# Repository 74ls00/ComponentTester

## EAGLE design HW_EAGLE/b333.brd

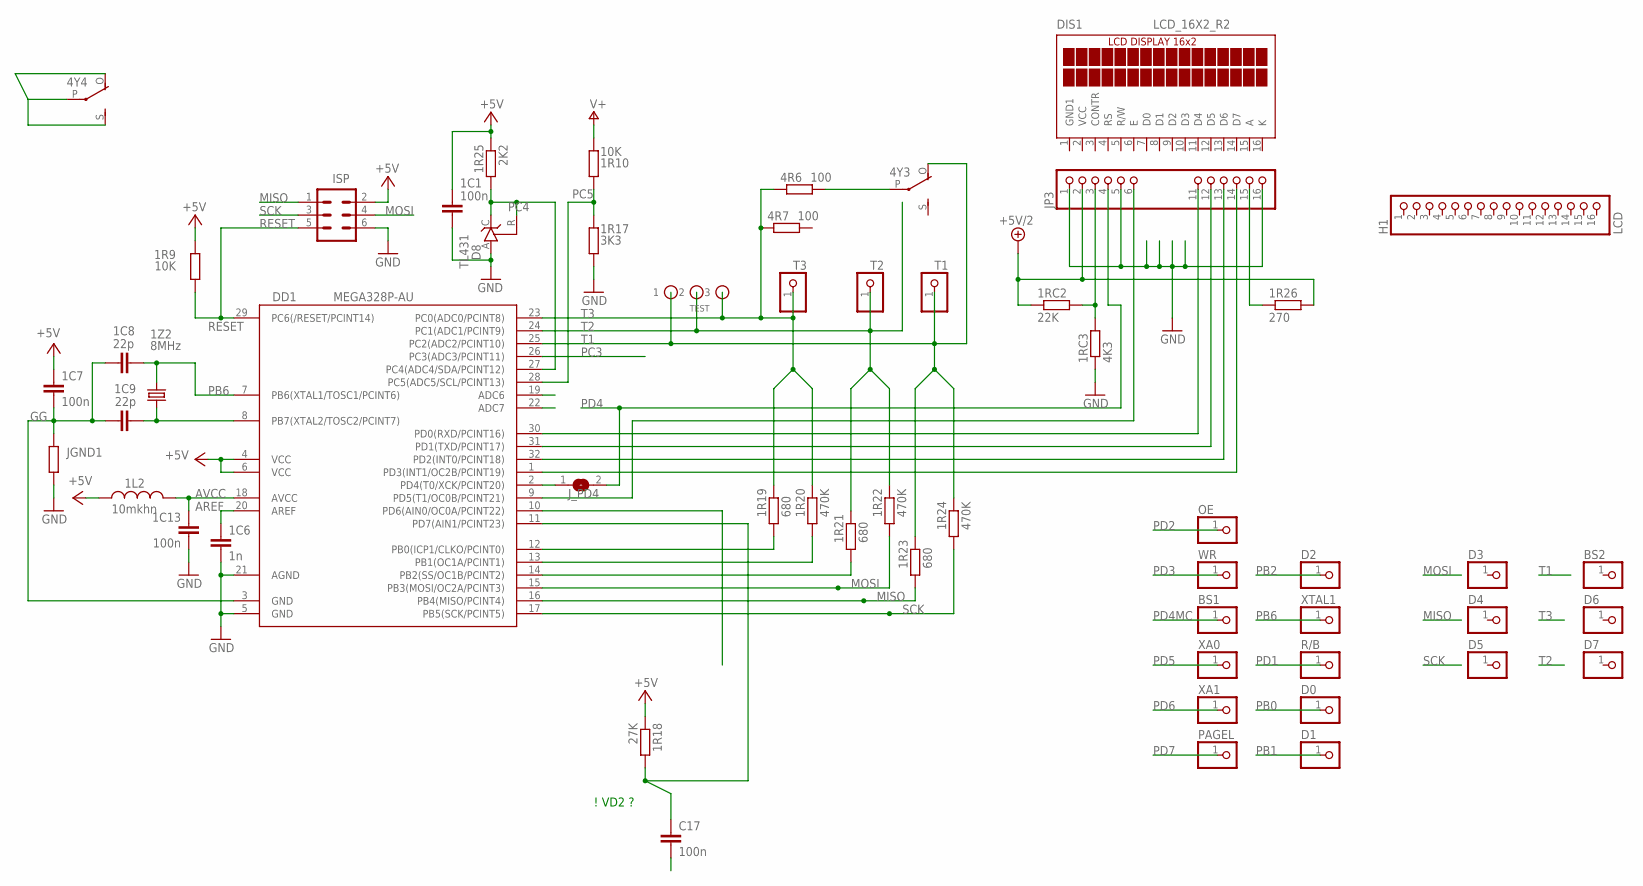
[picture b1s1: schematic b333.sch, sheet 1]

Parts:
1C1, 1C7, 1C13: 100n; C0805K
1C6: 1n; C0805K
1C8, 1C9: 22p; C0805K
1L2: 10mkhn; IRF36
1R9, 1R10: 10K; R0805
1R17: 3K3; R1206W
1R18: 27K; R0805
1R19, 1R21, 1R23: 680; M0805
1R20, 1R22, 1R24: 470K; M0805
1R25: 2K2; R0805
1R26: 270; R0805
1RC2: 22K; R0805
1RC3: 4K3; R1206W
1Z2: 8MHz; HC49U70
4R6, 4R7: 100; R0805
4Y3, 4Y4: РЭС55А
BS1, BS2: PINHD-1X1; 1X01
C17: 100n; C0805K
D0, D1, D2, D3, D4, D5, D6, D7: PINHD-1X1; 1X01
D8: TL431; TO92-CLP
DD1: MEGA328P-AU; TQFP32-08
DIS1: LCD_16X2_R2
H1: LCD; 1X16
ISP: MA03-2
JGND1: R-EU_R1206W; R1206W
JP3: PINHD-X16-8; 1X16-8
J_PD4: SJ
OE: PINHD-1X1; 1X01
PAGEL: PINHD-1X1; 1X01
R/B: PINHD-1X1; 1X01
T1, T2, T3: PINHD-1X1; 1X01
TEST: TT-P
WR: PINHD-1X1; 1X01
XA0, XA1: PINHD-1X1; 1X01
XTAL1: PINHD-1X1; 1X01

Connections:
+5V: 1C1.1, 1C7.1, 1L2.2, 1R9.2, 1R18.1, 1R25.1, DD1.4 (VCC), DD1.6 (VCC), ISP.2; also elsewhere on the board
+5V/2: 1R26.2, 1RC2.1, JP3.2; also elsewhere on the board
ADC6: DD1.19 (ADC6)
ADC7: DD1.22 (ADC7)
AREF: 1C6.1, DD1.20 (AREF)
AVCC: 1C13.1, 1L2.1, DD1.18 (AVCC)
GG: 1C7.2, 1C8.1, 1C9.1, DD1.3 (GND), JGND1.2
GND: 1C1.2, 1C6.2, 1C13.2, 1R17.1, 1RC3.1, C17.2, D8.A, DD1.5 (GND), DD1.21 (AGND), ISP.6, JGND1.1, JP3.1, JP3.5, JP3.16; also elsewhere on the board
GND1: DIS1.1 (GND1)
MISO: 1R23.1, DD1.16 (PB4(MISO/PCINT4)), ISP.1
MOSI: 1R22.1, DD1.15 (PB3(MOSI/OC2A/PCINT3)), ISP.4
unnamed: 4Y4.O, 4Y4.P, 4Y4.S
unnamed: 1RC2.2, 1RC3.2, JP3.3
unnamed: 1R26.1, JP3.15
unnamed: 1C9.2, 1Z2.1, DD1.8 (PB7(XTAL2/TOSC2/PCINT7))
unnamed: 4R6.2, 4Y3.P
PB0: 1R19.1, D0.1, DD1.12 (PB0(ICP1/CLKO/PCINT0))
PB1: 1R20.1, D1.1, DD1.13 (PB1(OC1A/PCINT1))
PB2: 1R21.1, D2.1, DD1.14 (PB2(SS/OC1B/PCINT2))
PB6: 1C8.2, 1Z2.2, DD1.7 (PB6(XTAL1/TOSC1/PCINT6)), XTAL1.1
PC3: DD1.26 (PC3(ADC3/PCINT11)); also elsewhere on the board
PC4: 1R25.2, D8.C, D8.R, DD1.27 (PC4(ADC4/SDA/PCINT12))
PC5: 1R10.2, 1R17.2, DD1.28 (PC5(ADC5/SCL/PCINT13))
PD0: DD1.30 (PD0(RXD/PCINT16)), JP3.11
PD1: DD1.31 (PD1(TXD/PCINT17)), JP3.12, R/B.1
PD2: DD1.32 (PD2(INT0/PCINT18)), JP3.13, OE.1
PD3: DD1.1 (PD3(INT1/OC2B/PCINT19)), JP3.14, WR.1; also elsewhere on the board
PD4: JP3.4, J_PD4.2
PD4MC: BS1.1, DD1.2 (PD4(T0/XCK/PCINT20)), J_PD4.1
PD5: DD1.9 (PD5(T1/OC0B/PCINT21)), JP3.6, XA0.1
PD6: DD1.10 (PD6(AIN0/OC0A/PCINT22)), XA1.1
PD7: 1R18.2, C17.1, DD1.11 (PD7(AIN1/PCINT23)), PAGEL.1
RESET: 1R9.1, DD1.29 (PC6(/RESET/PCINT14)), ISP.5
SCK: 1R24.1, DD1.17 (PB5(SCK/PCINT5)), ISP.3
T1: 1R23.2, 1R24.2, 4Y3.O, DD1.25 (PC2(ADC2/PCINT10)), T1.1, TEST.P$1 (1)
T2: 1R21.2, 1R22.2, DD1.24 (PC1(ADC1/PCINT9)), T2.1, TEST.P$2 (2), TEST.P$3 (2), TEST.P$4 (2)
T3: 1R19.2, 1R20.2, 4R6.1, 4R7.1, DD1.23 (PC0(ADC0/PCINT8)), T3.1, TEST.P$5 (3)
V+: 1R10.1; also elsewhere on the board
VCC: DIS1.2 (VCC)

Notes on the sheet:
! VD2 ?

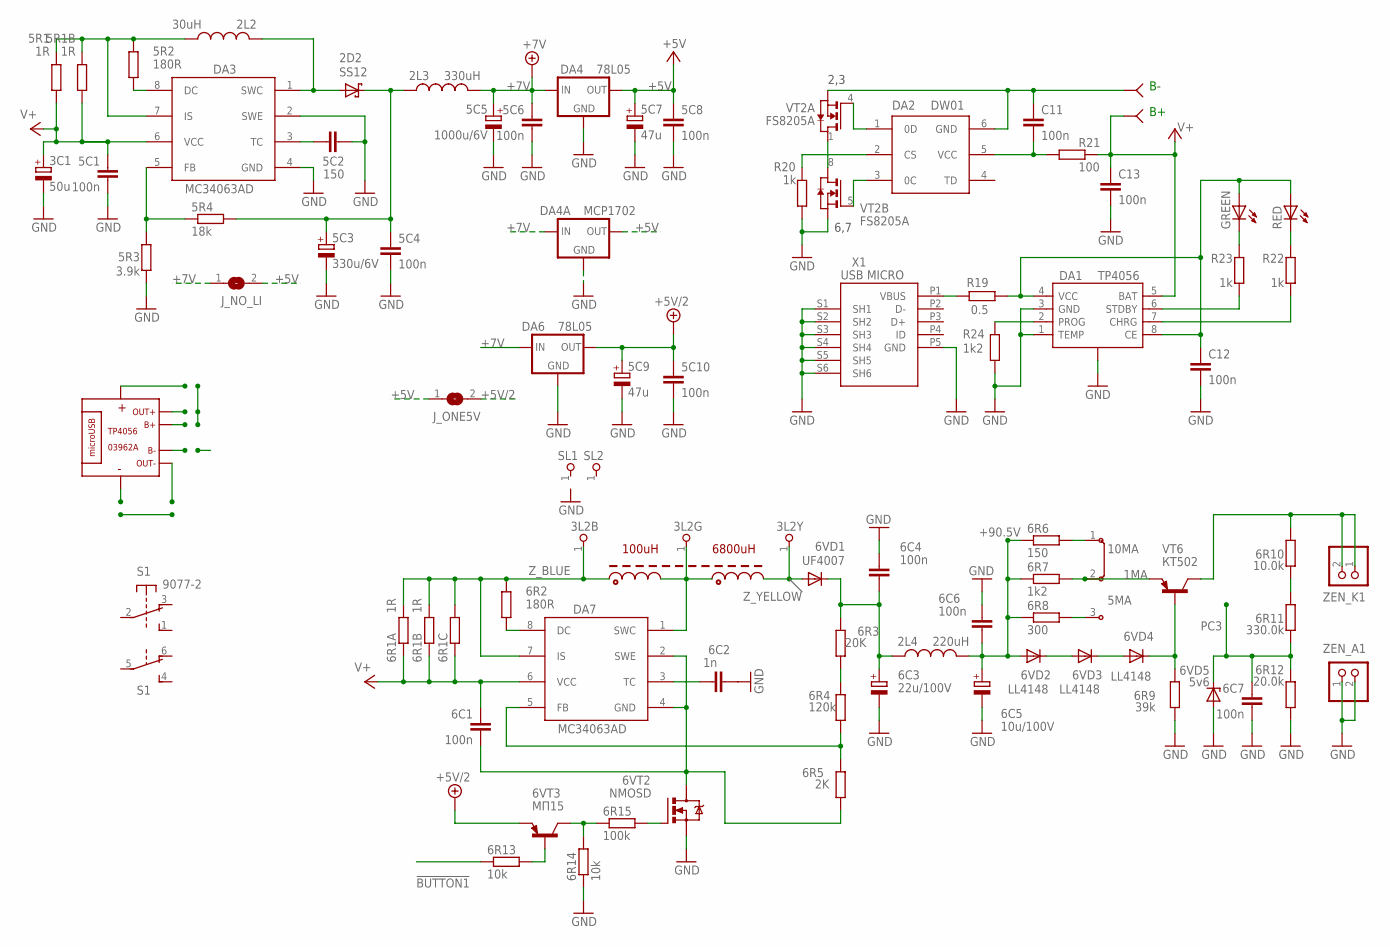
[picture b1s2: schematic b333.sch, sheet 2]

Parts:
2D2: SS12; SMB
2L2: 30uH; LH7X10MM
2L3: 330uH; LV7X10MM
2L4: 220uH; LV7X10MM
3C1: 50u; E2,5-6
3L2B, 3L2G, 3L2Y: PINHD-1X1; 1X01
5C1, 5C4, 5C6, 5C8, 5C10, 6C1: 100n; C0805K
5C2: 150; C0805K
5C3: 330u/6V; E2,5-7
5C5: 1000u/6V; E2-5
5C7, 5C9: 47u; E2,5-6
5MA: 10MA; JP2
5R1, 5R1B, 6R1A, 6R1B: 1R; R1206
5R2, 6R2: 180R; R0805
5R3: 3.9k; 0204/7
5R4: 18k; R0805
6C2: 1n; C0805K
6C3: 22u/100V; TT5D9L
6C4: 100n; C050-025X075
6C5: 10u/100V; E2,5-6
6C6, 6C7: 100n; C025-025X050
6R1C: R-EU_R1206; R1206
6R3: 20K; R0805
6R4: 120k; R0805
6R5: 2K; R0805
6R6: 150; R0805
6R7: 1k2; R0805
6R8: 300; R0805
6R9: 39k; R0805
6R10: 10.0k; R0805
6R11: 330.0k; R0805
6R12: 20.0k; R0805
6R13: 10k; R1206W
6R14: 10k; R0805
6R15: 100k; R1206W
6VD1: UF4007; DO41-10
6VD2, 6VD3, 6VD4: LL4148; SOD80C
6VD5: 5v6; SOD80C
6VT2: NMOSD; DPACK_1
6VT3: МП15; TO92-BCE
B+: B-; PAD-
B-: B-; PAD-
C11, C12, C13: 100n; C0805
DA1: TP4056; SOP-8
DA2: DW01A; SOT23-6
DA3, DA7: MC34063AD; SOIC8
DA4, DA6: 78L05; SOT89R
DA4A: MCP1702; SOT89R
GREEN: LED5MM
J_NO_LI: SJ
J_ONE5V: SJ
L: L
R19: 0.5; M0805
R20, R22, R23: 1k; R0805
R21: 100; R1206W
R24: 1k2; 0207/10
RED: LED5MM
S1: 9077-2
SL1, SL2: PINHD-1X1; 1X01
U$5: MOD_TP4056; MOD_03962A
VT2: FS8205A; TSSOP-8
VT6: КТ502; TO92-BCE
X1: USB MICRO; CON2_USB_MICRO_B_AT
ZEN_A1: PINHD-1X2; 1X02
ZEN_K1: PINHD-1X2; 1X02

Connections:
1MA: 5MA.2, 6R7.2, VT6.E
5: 6R4.1, 6R5.2, DA7.5 (FB)
!BUTTON1: 6R13.1
+5V: 5C7.+, 5C8.1, DA4.2 (OUT), DA4A.1 (OUT), J_NO_LI.2, J_ONE5V.1; also elsewhere on the board
+5V/2: 5C9.+, 5C10.1, 6VT3.E, DA6.2 (OUT), J_ONE5V.2; also elsewhere on the board
+7V: 2L3.2, 5C5.+, 5C6.1, DA4.1 (IN), DA4A.3 (IN), DA4A.4 (IN), DA6.1 (IN), J_NO_LI.1
+90.5V: 2L4.2, 6C5.+, 6C6.2, 6R6.1, 6R7.1, 6R8.1, 6VD2.A
B-: B-.B-, C11.1, DA2.6 (GND), VT2.2 (S), VT2.3 (S)
GND: 3C1.-, 5C1.2, 5C2.2, 5C3.-, 5C4.2, 5C5.-, 5C6.2, 5C7.-, 5C8.2, 5C9.-, 5C10.2, 5R3.1, 6C2.2, 6C3.-, 6C4.1, 6C5.-, 6C6.1, 6C7.2, 6R9.1, 6R12.1, 6R14.1, 6VD5.A, 6VT2.S, C12.2, C13.2, DA1.1 (TEMP), DA1.3 (GND), DA1.., DA3.2 (SWE), DA3.4 (GND), DA4.3 (GND), DA4.4 (GND), DA4A.2 (GND), DA6.3 (GND), DA6.4 (GND), R20.1, R24.1, VT2.6 (S), VT2.7 (S), X1.P5 (GND), X1.S1 (SH1), X1.S2 (SH2), X1.S3 (SH3), X1.S4 (SH4), X1.S5 (SH5), X1.S6 (SH6), ZEN_A1.1, ZEN_A1.2; also elsewhere on the board
unnamed: R22.2, RED.K (C)
unnamed: GREEN.K (C), R23.2
unnamed: 5C2.1, DA3.3 (TC)
unnamed: 6C1.2, 6R5.1, 6VT2.D, DA7.2 (SWE), DA7.4 (GND)
unnamed: 2D2.A, 2L2.1, DA3.1 (SWC)
unnamed: 2L2.2, 5R1.2, 5R1B.2, 5R2.1, DA3.7 (IS)
unnamed: 5R2.2, DA3.8 (DC)
unnamed: 5R3.2, 5R4.1, DA3.5 (FB)
unnamed: 2D2.C, 2L3.1, 5C3.+, 5C4.1, 5R4.2
unnamed: 2L4.1, 6C3.+, 6C4.2, 6R3.2, 6VD1.C
unnamed: 6R14.2, 6R15.1, 6VT3.C
unnamed: 6C2.1, DA7.3 (TC)
unnamed: 6R3.1, 6R4.2
unnamed: 6R10.1, 6R11.2
unnamed: 6R2.2, DA7.8 (DC)
unnamed: 5MA.3, 6R8.2
unnamed: 5MA.1, 6R6.2
unnamed: 6VD2.C, 6VD3.A
unnamed: 6VD3.C, 6VD4.A
unnamed: 6R9.2, 6VD4.C, VT6.B
unnamed: VT2.1 (D), VT2.8 (D)
unnamed: DA2.3 (0C), VT2.5 (G)
unnamed: DA2.1 (0D), VT2.4 (G)
unnamed: DA2.2 (CS), R20.2
unnamed: C11.2, DA2.5 (VCC), R21.1
unnamed: DA1.7 (CHRG), R22.1
unnamed: DA1.6 (STDBY), R23.1
unnamed: C12.1, DA1.4 (VCC), DA1.8 (CE), GREEN.A, R19.2, RED.A
unnamed: R19.1, X1.P1 (VBUS)
unnamed: DA1.2 (PROG), R24.2
unnamed: 6R13.2, 6VT3.B
unnamed: 6R15.2, 6VT2.G
PC3: 6C7.1, 6R11.1, 6R12.2, 6VD5.C; also elsewhere on the board
V+: 3C1.+, 5C1.1, 5R1.1, 5R1B.1, 6C1.1, 6R1A.1, 6R1B.1, 6R1C.1, B+.B-, C13.1, DA1.5 (BAT), DA3.6 (VCC), DA7.6 (VCC), R21.2; also elsewhere on the board
ZENER: 6R10.2, VT6.C, ZEN_K1.1, ZEN_K1.2
Z_BLUE: 3L2B.1, 6R1A.2, 6R1B.2, 6R1C.2, 6R2.1, DA7.7 (IS)
Z_GREEN: 3L2G.1, DA7.1 (SWC)
Z_YELLOW: 3L2Y.1, 6VD1.A

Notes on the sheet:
6800uH
100uH
2,3
6,7

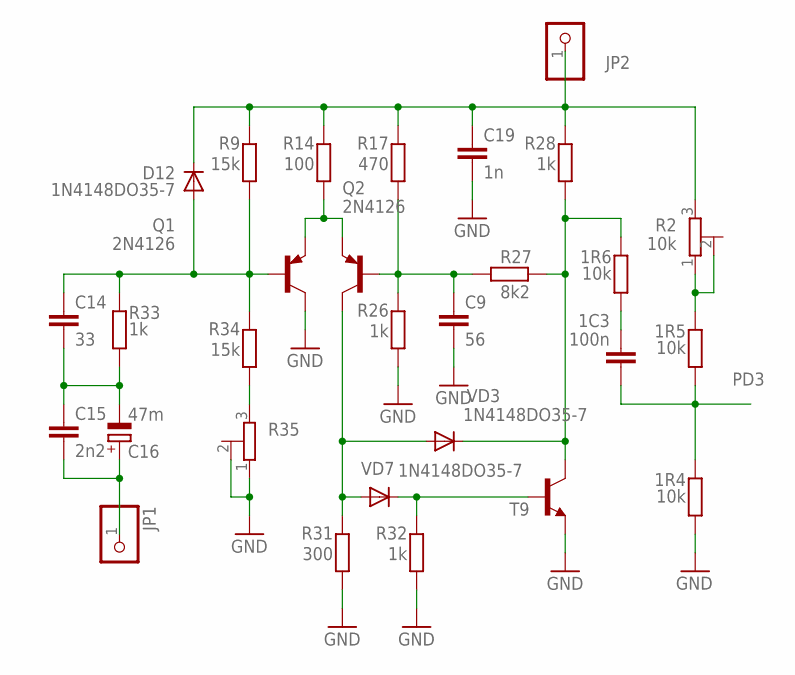
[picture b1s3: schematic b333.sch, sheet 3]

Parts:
1C3: 100n; C0805K
1R4, 1R5, 1R6: 10k; R0805
C9: 56; C0805K
C14: 33; C0805K
C15: 2n2; C0805K
C16: 47m; E2-4
C19: 1n; C0805K
D12: 1N4148DO35-7; DO35-7
JP1, JP2: PINHD-1X1; 1X01
Q1, Q2: 2N4126; TO92-CBE
R2: 10k; RTRIM3296W
R9, R34: 15k; M0805
R14: 100; M0805
R17: 470; M0805
R26, R28, R32, R33: 1k; M0805
R27: 8k2; M0805
R31: 300; M0805
R35: R-TRIMM3296W; RTRIM3296W
T9: -NPN-TO92-EBC; TO92-EBC
VD3, VD7: 1N4148DO35-7; DO35-7

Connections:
FO: 1R6.2, R27.2, R28.1, T9.C, VD3.C
GND: 1R4.1, C9.2, C19.2, Q1.C, R26.1, R31.1, R32.1, R35.1 (A), R35.2 (S), T9.E; also elsewhere on the board
unnamed: C19.1, D12.C, JP2.1, R2.3 (E), R9.2, R14.2, R17.2, R28.2
unnamed: R34.1, R35.3 (E)
unnamed: 1R5.2, R2.1 (A), R2.2 (S)
unnamed: 1C3.1, 1R6.1
unnamed: Q1.E, Q2.E, R14.1
unnamed: C14.1, D12.A, Q1.B, R9.1, R33.2, R34.2
unnamed: C9.1, Q2.B, R17.1, R26.2, R27.1
unnamed: Q2.C, R31.2, VD3.A, VD7.A
unnamed: C14.2, C15.1, C16.-, R33.1
unnamed: R32.2, T9.B, VD7.C
unnamed: C15.2, C16.+, JP1.1
PD3: 1C3.2, 1R4.2, 1R5.1; also elsewhere on the board

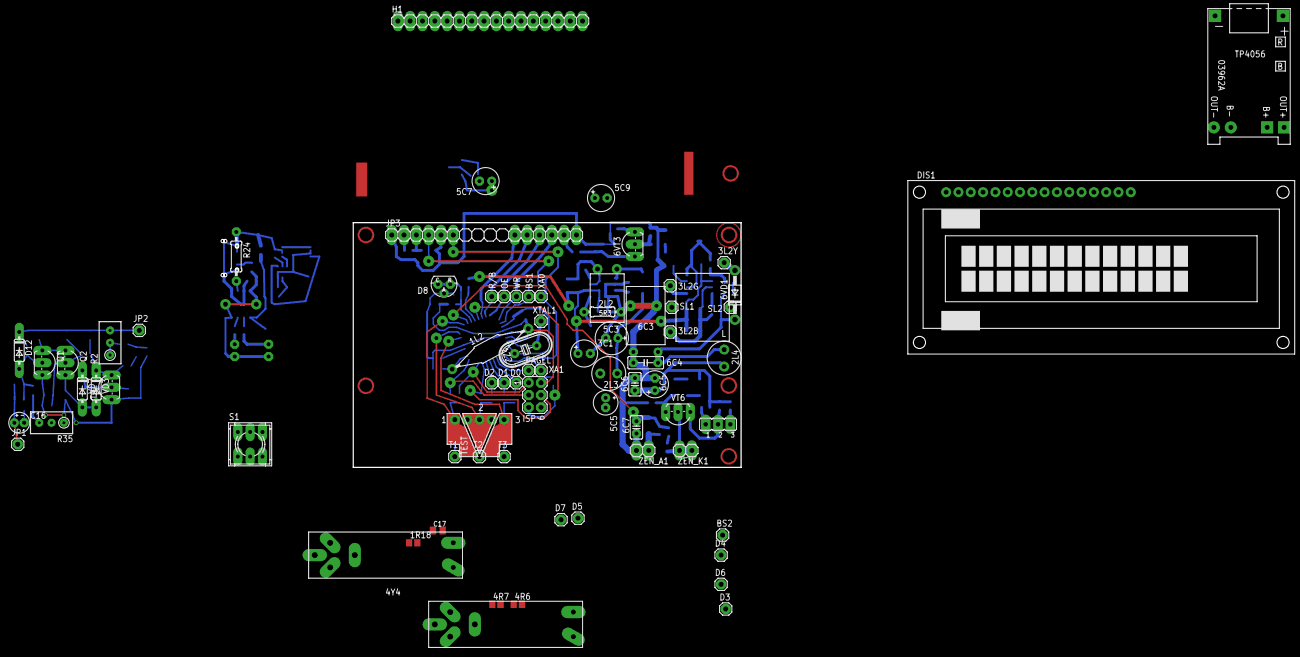
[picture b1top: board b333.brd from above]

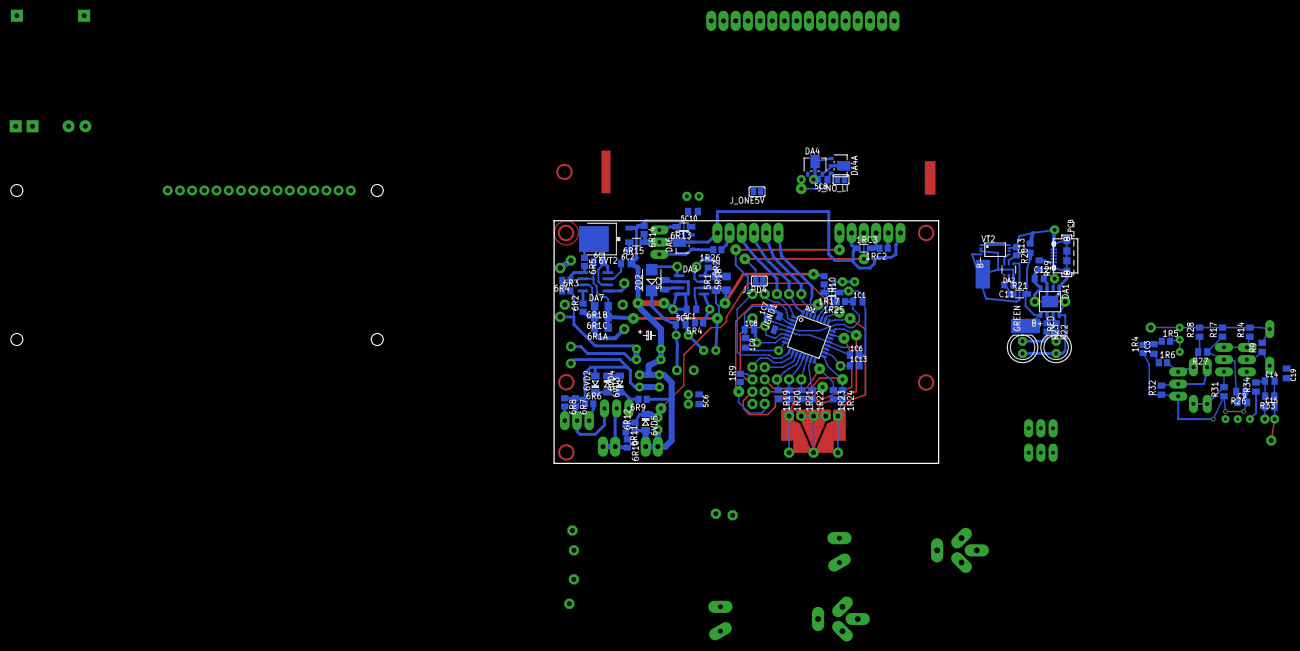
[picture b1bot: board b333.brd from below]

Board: 2 copper layers, 80.0 x 50.5 mm, 174 parts (98 on the bottom side), 88 nets.

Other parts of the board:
U$8, U$11: F18650

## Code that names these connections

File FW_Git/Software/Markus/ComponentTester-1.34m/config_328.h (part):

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#define LCD_PORT         PORTD          /* port data register */
#define LCD_DDR          DDRD           /* port data direction register */
#define LCD_DB_STD                      /* use standard pins 0-3 for DB4-7 */
#define LCD_DB4          PD0            /* port pin used for DB4 */
#define LCD_DB5          PD1            /* port pin used for DB5 */
#define LCD_DB6          PD2            /* port pin used for DB6 */
#define LCD_DB7          PD3            /* port pin used for DB7 */
#define LCD_RS           PD4            /* port pin used for RS */
#define LCD_EN1          PD5            /* port pin used for E */
#define LCD_CHAR_X       16             /* characters per line */
#define LCD_CHAR_Y       2              /* number of lines */
#define FONT_HD44780_INT                /* internal 5x7 font: international */
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#define I2C_PORT         PORTD          /* I2C port data register */
#define I2C_DDR          DDRD           /* I2C port data direction register */
#define I2C_PIN          PIND           /* I2C port input pins register */
#define I2C_SDA          PD0            /* port pin used for SDA */
#define I2C_SCL          PD1            /* port pin used for SCL */
#endif


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/*
 *  ST7565R, SPI interface (bit-bang)
 *  - settings for Electronic Assembly EA DOGM/DOGL128-6
 *  - uses LCD_CS to support rotary encoder in parallel at PD2/3
 */

#if 0
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#define LCD_SPI                         /* SPI interface */
#define LCD_PORT         PORTD          /* port data register */
#define LCD_DDR          DDRD           /* port data direction register */
#define LCD_RESET        PD0            /* port pin used for /RES (optional) */
#define LCD_CS           PD5            /* port pin used for /CS1 (optional) */
#define LCD_A0           PD1            /* port pin used for A0 */
#define LCD_SCL          PD2            /* port pin used for SCL */
#define LCD_SI           PD3            /* port pin used for SI (LCD's data input) */
#define LCD_DOTS_X       128            /* number of horizontal dots */
#define LCD_DOTS_Y       64             /* number of vertical dots */
//#define LCD_FLIP_X                      /* enable horizontal flip */
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#define LCD_SPI                         /* SPI interface */
#define LCD_PORT         PORTD          /* port data register */
#define LCD_DDR          DDRD           /* port data direction register */
#define LCD_RES          PD4            /* port pin used for /RES (optional) */
#define LCD_CS           PD5            /* port pin used for /CS (optional) */
#define LCD_DC           PD3            /* port pin used for D/C */
#define LCD_SCK          PD2            /* port pin used for SCK */
#define LCD_SDI          PD1            /* port pin used for SDI (LCD's data input) */
//#define LCD_SDO          PD0            /* port pin used for SDO (LCD's data output) */
#define LCD_DOTS_X       320            /* number of horizontal dots */
#define LCD_DOTS_Y       240            /* number of vertical dots */
//#define LCD_FLIP_X                      /* enable horizontal flip */
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#define LCD_SPI                         /* SPI interface */
#define LCD_PORT         PORTD          /* port data register */
#define LCD_DDR          DDRD           /* port data direction register */
#define LCD_RES          PD4            /* port pin used for /RESX (optional) */
#define LCD_CS           PD5            /* port pin used for /CSX (optional) */
#define LCD_DC           PD3            /* port pin used for D/CX */
#define LCD_SCL          PD2            /* port pin used for SCL */
#define LCD_SDA          PD1            /* port pin used for SDA */
#define LCD_DOTS_X       128            /* number of horizontal dots */
#define LCD_DOTS_Y       160            /* number of vertical dots */
//#define LCD_FLIP_X                      /* enable horizontal flip */
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#define LCD_SPI                         /* SPI interface */
#define LCD_PORT         PORTD          /* port data register */
#define LCD_DDR          DDRD           /* port data direction register */
#define LCD_RES          PD4            /* port pin used for /RES (optional) */
#define LCD_SCE          PD5            /* port pin used for /SCE (optional) */
#define LCD_DC           PD3            /* port pin used for D/C */
#define LCD_SCLK         PD2            /* port pin used for SCLK */
#define LCD_SDIN         PD1            /* port pin used for SDIN (LCD's data input) */
#define LCD_DOTS_X       84             /* number of horizontal dots */
#define LCD_DOTS_Y       48             /* number of vertical dots */
#define LCD_CONTRAST     66             /* default contrast (1-127) */
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#define LCD_SPI                         /* SPI interface */
#define LCD_PORT         PORTD          /* port data register */
#define LCD_DDR          DDRD           /* port data direction register */
#define LCD_RESET        PD4            /* port pin used for /RESET (optional) */
#define LCD_CS           PD5            /* port pin used for CS (optional) */
#define LCD_SCLK         PD2            /* port pin used for SCLK */
#define LCD_SID          PD1            /* port pin used for SID (LCD's data input) */
#define LCD_DOTS_X       128            /* number of horizontal dots */
#define LCD_DOTS_Y       64             /* number of vertical dots */
#define FONT_8X8_H                      /* 8x8 font, horizonally aligned */
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#define LCD_PORT         PORTD          /* port data register */
#define LCD_DDR          DDRD           /* port data direction register */
#define LCD_DB_STD                      /* use standard pins 0-3 for DB4-7 */
#define LCD_DB4          PD0            /* port pin used for DB4 */
#define LCD_DB5          PD1            /* port pin used for DB5 */
#define LCD_DB6          PD2            /* port pin used for DB6 */
#define LCD_DB7          PD3            /* port pin used for DB7 */
#define LCD_RS           PD4            /* port pin used for RS */
#define LCD_EN           PD5            /* port pin used for E */
#define LCD_DOTS_X       128            /* number of horizontal dots */
#define LCD_DOTS_Y       64             /* number of vertical dots */
#define FONT_8X8_H                      /* 8x8 font, horizonally aligned */
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#define LCD_SPI                         /* SPI interface */
#define LCD_PORT         PORTD          /* port data register */
#define LCD_DDR          DDRD           /* port data direction register */
#define LCD_RES          PD4            /* port pin used for /RESX (optional) */
#define LCD_CS           PD5            /* port pin used for /CSX (optional) */
#define LCD_DC           PD3            /* port pin used for D/CX */
#define LCD_SCL          PD2            /* port pin used for SCL */
#define LCD_SDA          PD1            /* port pin used for SDA/SDIO */
#define LCD_DOTS_X       128            /* number of horizontal dots */
#define LCD_DOTS_Y       128            /* number of vertical dots */
#define LCD_OFFSET_X      32            /* x offset of 32 dots (160-128) */
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#define LCD_SPI                         /* SPI interface */
#define LCD_PORT         PORTD          /* port data register */
#define LCD_DDR          DDRD           /* port data direction register */
#define LCD_RESET        PD4            /* port pin used for /RES (optional) */
#define LCD_CS           PD5            /* port pin used for /CS (optional) */
#define LCD_DC           PD3            /* port pin used for D/C */
#define LCD_SCLK         PD2            /* port pin used for SCLK */
#define LCD_SDIN         PD1            /* port pin used for SDIN (LCD's data input) */
#define LCD_DOTS_X       128            /* number of horizontal dots */
#define LCD_DOTS_Y       64             /* number of vertical dots */
#define LCD_FLIP_X                      /* enable horizontal flip */
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#define LCD_I2C_ADDR     0x3c           /* SSD1306's I2C address */
#define LCD_PORT         PORTD          /* port data register */
#define LCD_DDR          DDRD           /* port data direction register */
#define LCD_RESET        PD4            /* port pin used for /RES (optional) */
#define LCD_DOTS_X       128            /* number of horizontal dots */
#define LCD_DOTS_Y       64             /* number of vertical dots */
#define LCD_FLIP_X                      /* enable horizontal flip */
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#define I2C_PORT         PORTD          /* I2C port data register */
#define I2C_DDR          DDRD           /* I2C port data direction register */
#define I2C_PIN          PIND           /* I2C port input pins register */
#define I2C_SDA          PD0            /* port pin used for SDA */
#define I2C_SCL          PD1            /* port pin used for SCL */
#endif


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#define ADC_PORT         PORTC     /* ADC port data register */
#define ADC_DDR          DDRC      /* ADC port data direction register */
#define ADC_PIN          PINC      /* port input pins register */
#define TP1              PC0       /* test pin 1 */
#define TP2              PC1       /* test pin 2 */
#define TP3              PC2       /* test pin 3 */
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
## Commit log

2018-10-16 1.34m
2018-10-16 add docu
2018-10-16 add my fw
2018-10-18 add htm
2018-10-19 add devmgr
2018-10-21 34063 links
2018-10-21 add lnk
2018-10-24 home
2018-10-25 -rcllbr
2018-10-26 relbr
2018-10-26 reorg
2018-10-26 rtrim
2018-11-14 pp pin

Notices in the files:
FW_Git/Software/Markus/ComponentTester-1.34m/config_328.h:
(c) 2012-2018 by Markus Reschke
